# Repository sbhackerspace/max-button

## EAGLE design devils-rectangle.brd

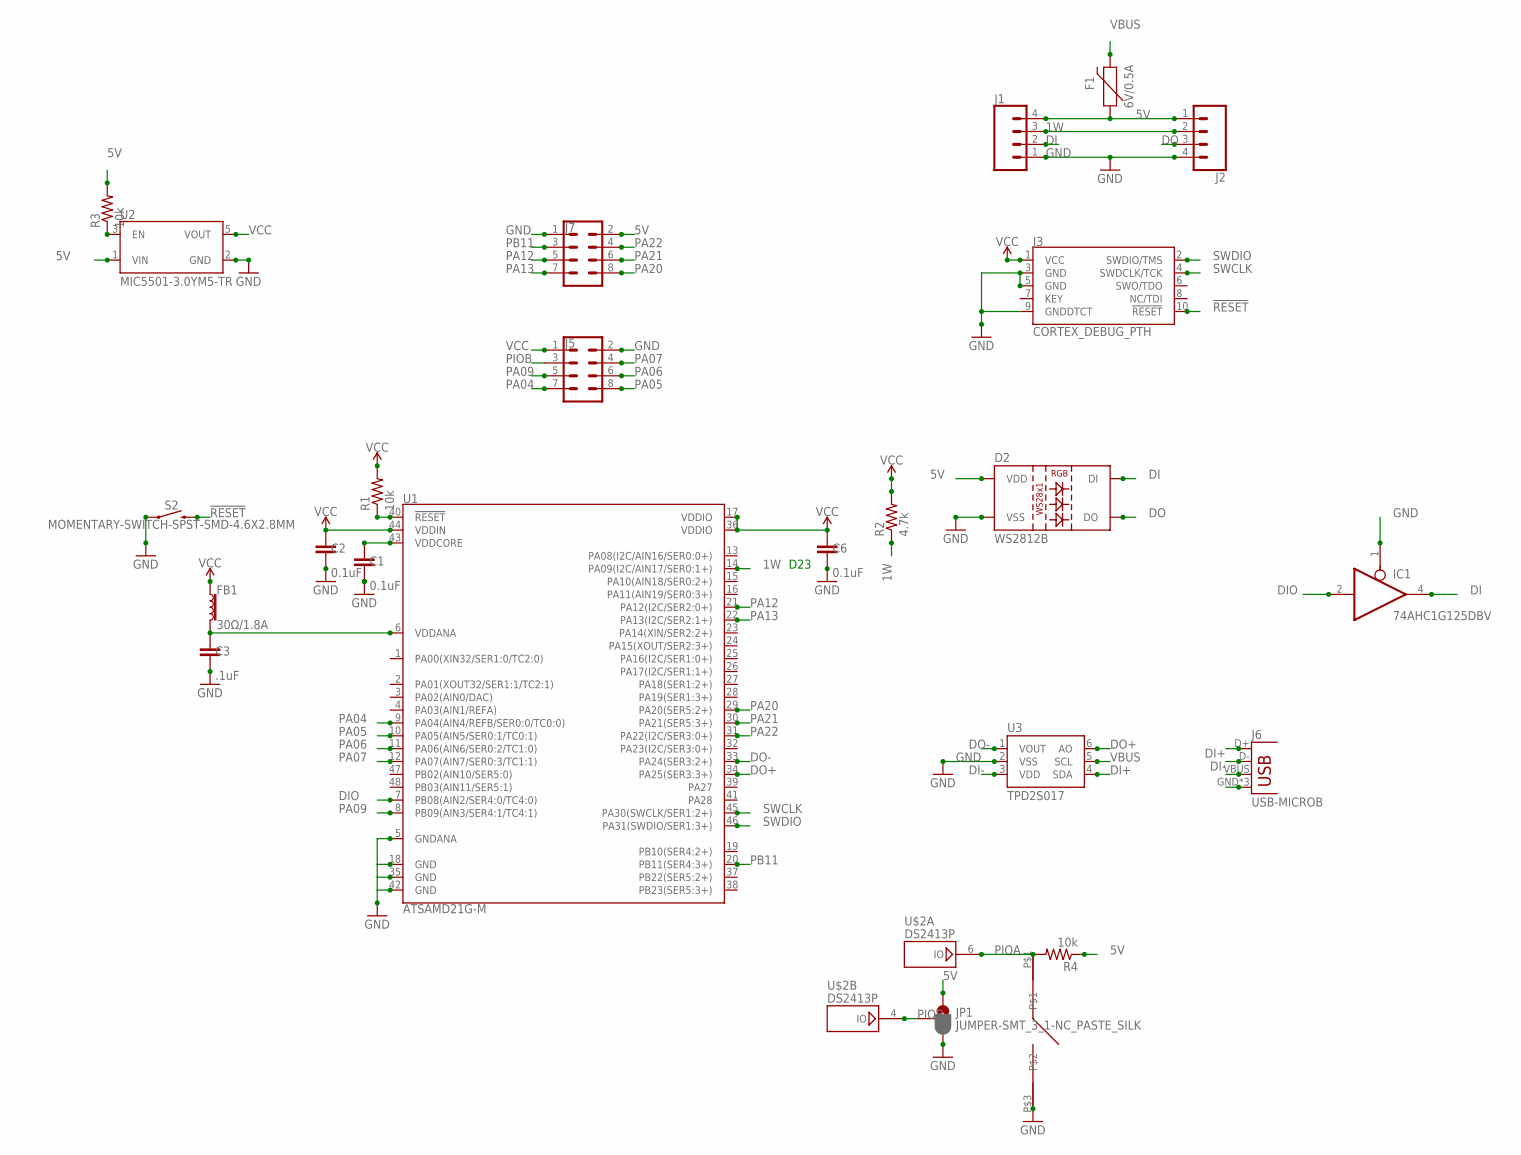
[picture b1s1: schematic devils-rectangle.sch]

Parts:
C1, C2, C6: 0.1uF; 0402
C3: .1uF; 0402
D2: WS2812B
F1: 6V/0.5A; 1206
FB1: 30Ω/1.8A; 0603
IC1: 74AHC1G125DBV; SOT23-5
J1, J2: CONN_04SMD2; 1X04_1MM_RA
J3: CORTEX_DEBUG_PTH; 2X5-PTH-1.27MM
J5, J7: CONN_04X2; 2X4
J6: USB-MICROB
JP1: JUMPER-SMT_3_1-NC_PASTE_SILK; SMT-JUMPER_3_1-NC_PASTE_SILK
R1, R3, R4: 10k; R0402
R2: 4.7k; R0402
S2: MOMENTARY-SWITCH-SPST-SMD-4.6X2.8MM; TACTILE_SWITCH_SMD_4.6X2.8MM
U1: ATSAMD21G-M; QFN-48
U2: MIC5501-3.0YM5-TR; SOT95P280X145-5N
U3: TPD2S017; SOT23-6
U$1: NOVELKEY
U$2: DS2413P; TSOC6

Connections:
1W: J1.3, J2.2, R2.1, U1.14 (PA09(I2C/AIN17/SER0:1+)), U$2.2 (1W)
5V: D2.1 (VDD), F1.1, IC1.5 (5V), J1.4, J2.1, J7.2, JP1.1, R3.2, R4.1, U2.1 (VIN)
!RESET: J3.10 (!RESET), R1.1, S2.3 (2), S2.4 (2), U1.40 (!RESET!)
DI: D2.4 (DI), IC1.4 (O), J1.2
DI+: J6.D+, U3.4 (SDA)
DI-: J6.D-, U3.3 (VDD)
DIO: IC1.2 (I), U1.7 (PB08(AIN2/SER4:0/TC4:0))
DO: D2.2 (DO), J2.3
DO+: U1.34 (PA25(SER3:3+)), U3.6 (AO)
DO-: U1.33 (PA24(SER3:2+)), U3.1 (VOUT)
GND: C1.2, C2.2, C3.2, C6.2, D2.3 (VSS), IC1.1 (OE), IC1.3 (GND), J1.1, J2.4, J3.3 (GND), J3.5 (GND), J3.9 (GNDDTCT), J5.2, J6.GND, J6.MT1 (GND), J6.MT2 (GND), J7.1, JP1.3, S2.1, S2.2 (1), U1.5 (GNDANA), U1.18 (GND), U1.35 (GND), U1.42 (GND), U2.2 (GND), U3.2 (VSS), U$1.P$3, U$2.1 (GND), U$2.5 (GND)
unnamed: R3.1, U2.3 (EN)
unnamed: C3.1, FB1.2, U1.6 (VDDANA)
unnamed: C1.1, U1.43 (VDDCORE)
PA04: J5.7, U1.9 (PA04(AIN4/REFB/SER0:0/TC0:0))
PA05: J5.8, U1.10 (PA05(AIN5/SER0:1/TC0:1))
PA06: J5.6, U1.11 (PA06(AIN6/SER0:2/TC1:0))
PA07: J5.4, U1.12 (PA07(AIN7/SER0:3/TC1:1))
PA09: J5.5, U1.8 (PB09(AIN3/SER4:1/TC4:1))
PA12: J7.5, U1.21 (PA12(I2C/SER2:0+))
PA13: J7.7, U1.22 (PA13(I2C/SER2:1+))
PA20: J7.8, U1.29 (PA20(SER5:2+))
PA21: J7.6, U1.30 (PA21(SER5:3+))
PA22: J7.4, U1.31 (PA22(I2C/SER3:0+))
PB11: J7.3, U1.20 (PB11(SER4:3+))
PIOA: R4.2, U$1.P$1, U$2.6 (IO)
PIOB: J5.3, JP1.2, U$2.4 (IO)
SWCLK: J3.4 (SWDCLK/TCK), U1.45 (PA30(SWCLK/SER1:2+))
SWDIO: J3.2 (SWDIO/TMS), U1.46 (PA31(SWDIO/SER1:3+))
VBUS: F1.2, J6.VBUS, U3.5 (SCL)
VCC: C2.1, C6.1, FB1.1, J3.1 (VCC), J5.1, R1.2, R2.2, U1.17 (VDDIO), U1.36 (VDDIO), U1.44 (VDDIN), U2.5 (VOUT)

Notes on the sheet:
D23

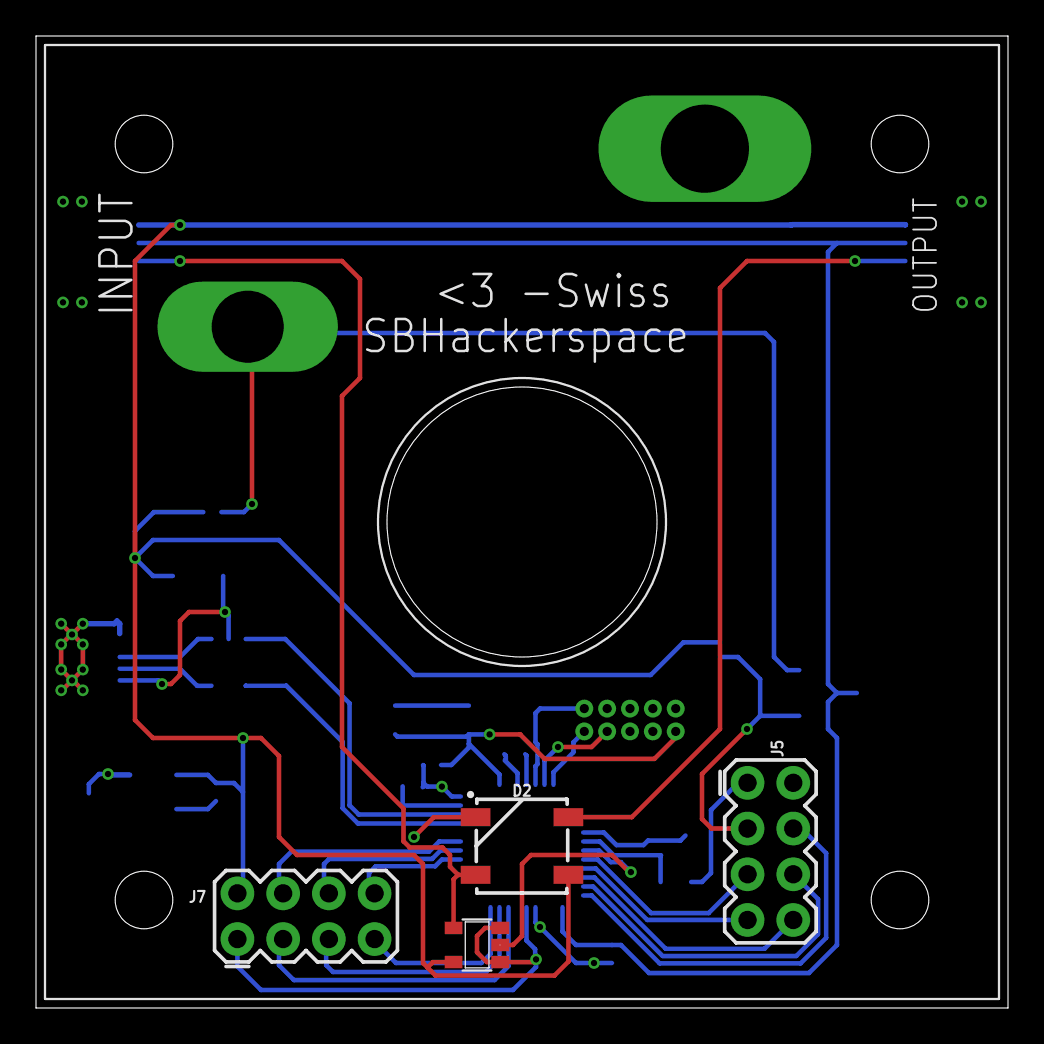
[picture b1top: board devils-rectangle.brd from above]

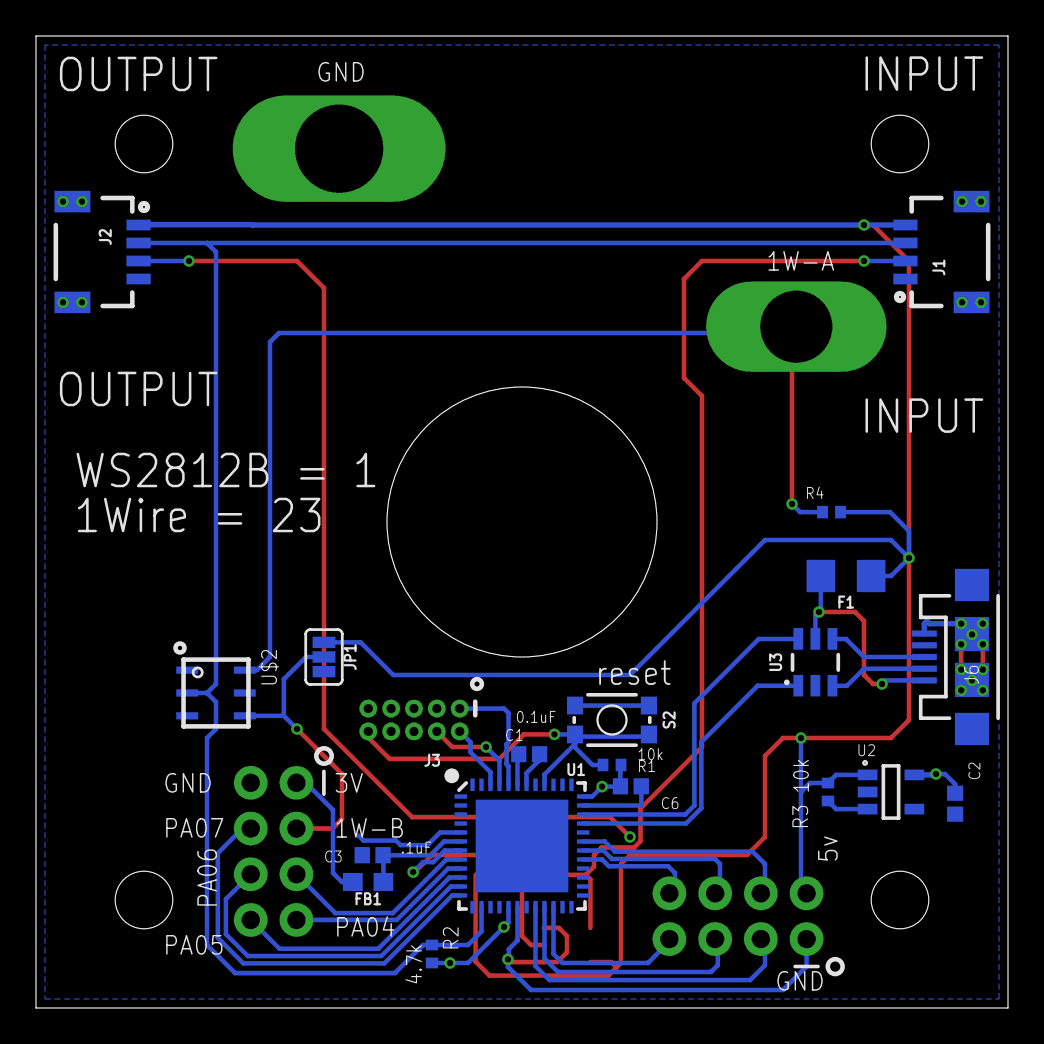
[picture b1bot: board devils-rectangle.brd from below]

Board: 2 copper layers, 54.0 x 54.0 mm, 25 parts (20 on the bottom side), 31 nets.

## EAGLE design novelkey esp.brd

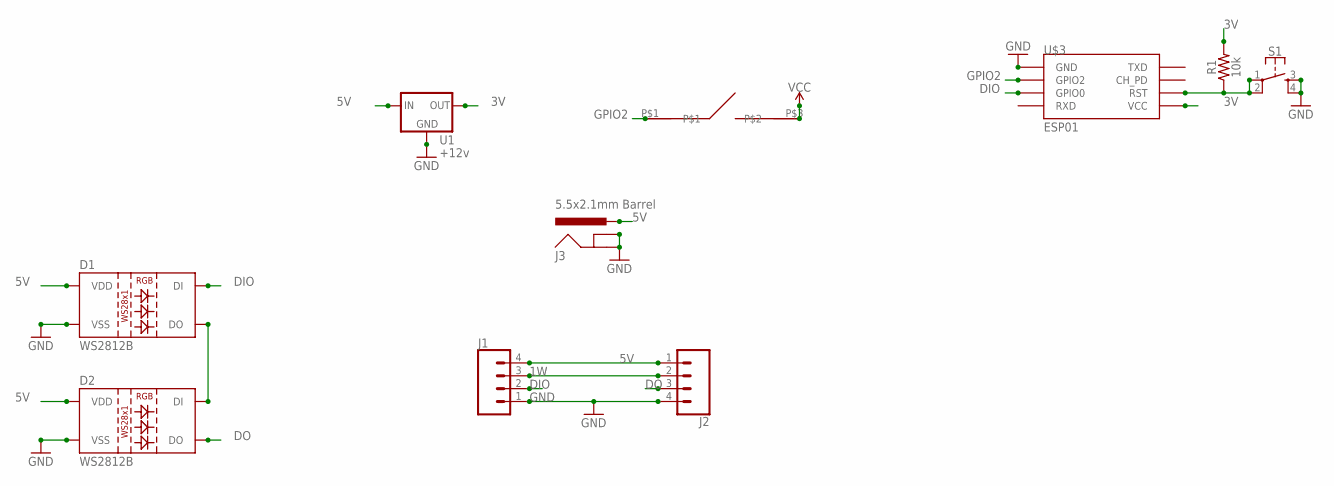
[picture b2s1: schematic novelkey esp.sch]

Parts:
D1, D2: WS2812B
J1, J2: CONN_04SMD2; 1X04_1MM_RA
J3: 5.5x2.1mm Barrel; POWER_JACK_SMD
R1: 10k; 0603
S1: MOMENTARY-SWITCH-SPST-2-SMD-4.6X2.8MM; TACTILE_SWITCH_SMD_4.6X2.8MM
U1: +12v; TO-252
U$1: NOVELKEY
U$3: ESP01

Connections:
1W: J1.3, J2.2
3V: R1.2, U1.2 (OUT), U$3.VCC
5V: D1.1 (VDD), D2.1 (VDD), J1.4, J2.1, J3.VIN0 (PWR), U1.1 (IN)
DIO: D1.4 (DI), J1.2, U$3.GPIO0
DO: D2.2 (DO), J2.3
GND: D1.3 (VSS), D2.3 (VSS), J1.1, J2.4, J3.GND (GNDBREAK), J3.P$4 (GND), S1.3, S1.4, U1.3 (GND), U$3.GND
GPIO2: U$1.P$1, U$3.GPIO2
unnamed: R1.1, S1.1, S1.2, U$3.RST
unnamed: D1.2 (DO), D2.4 (DI)
VCC: U$1.P$3

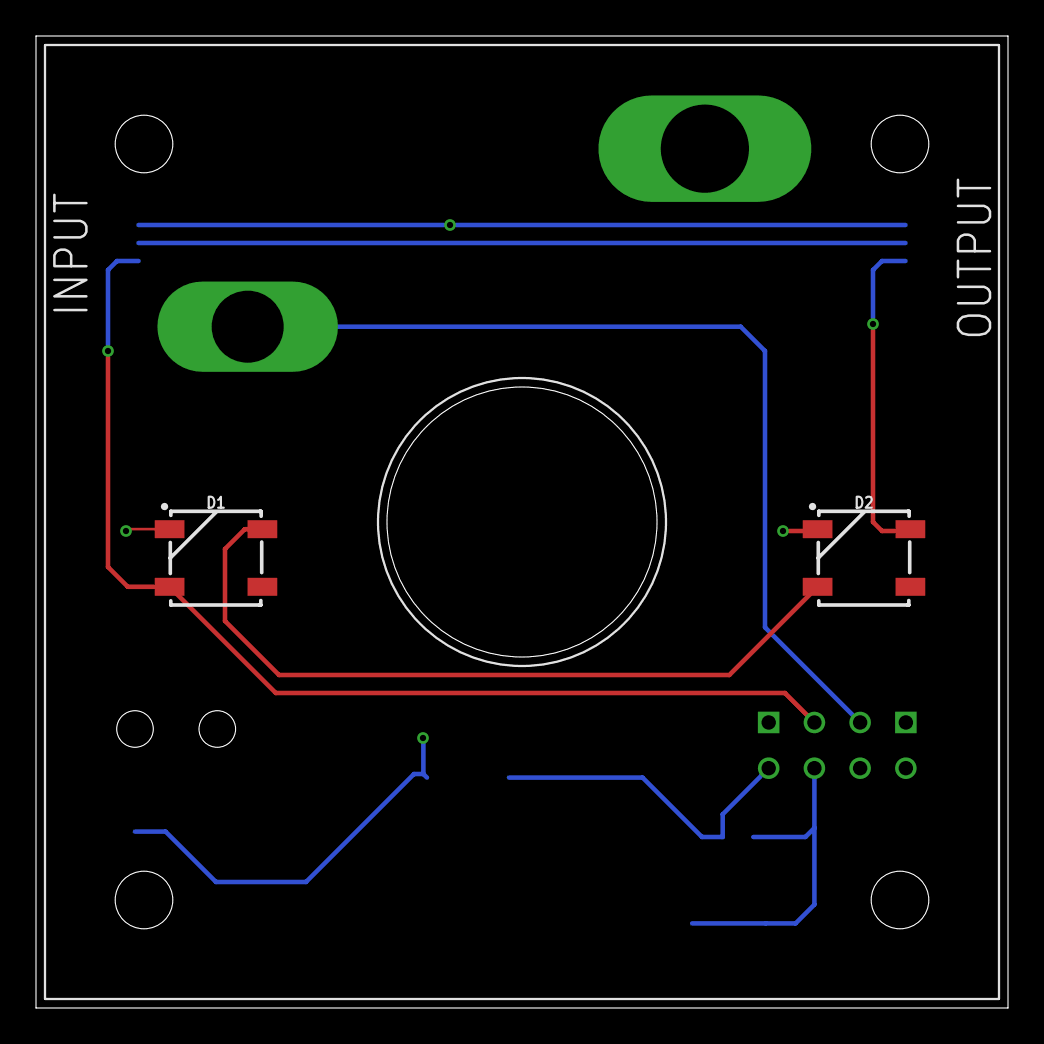
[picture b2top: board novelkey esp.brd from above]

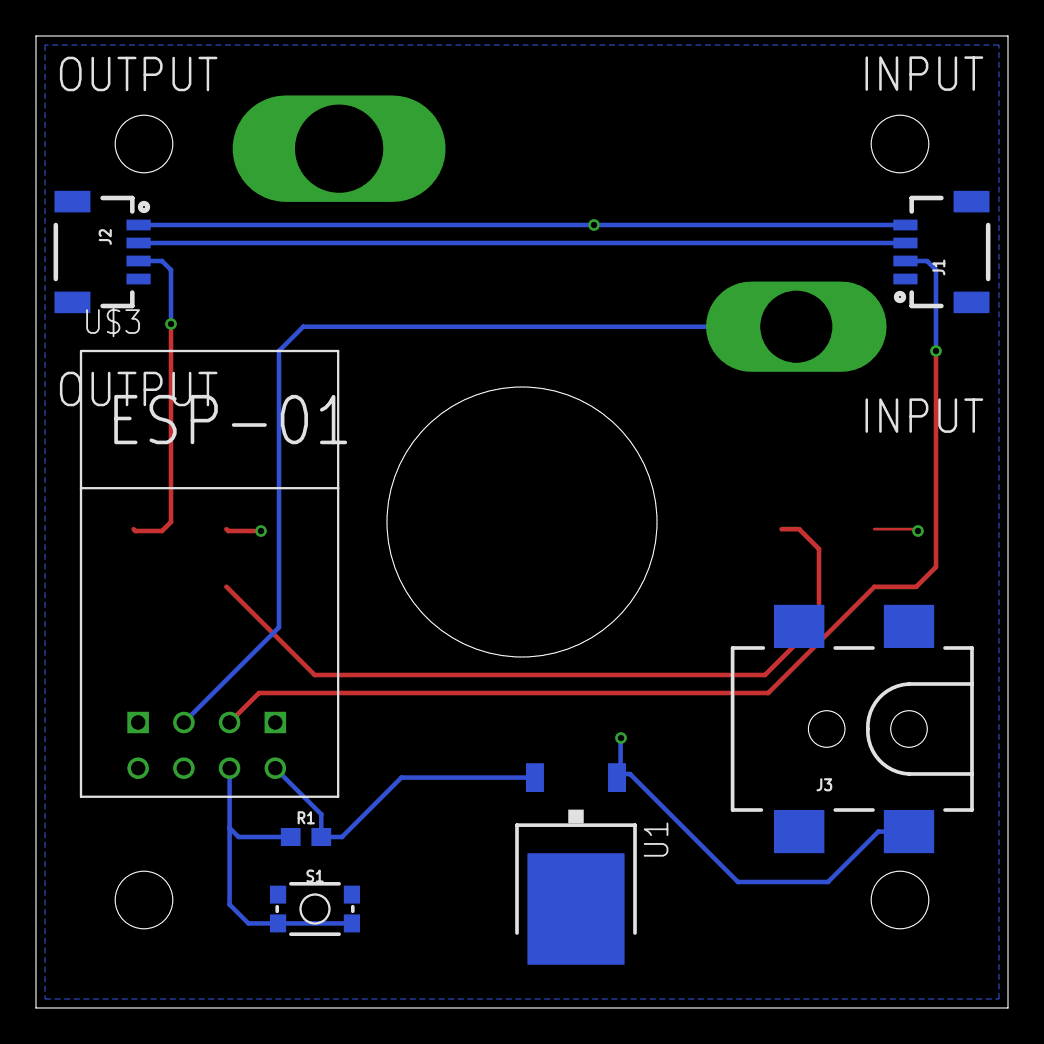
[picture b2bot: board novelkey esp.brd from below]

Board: 2 copper layers, 54.0 x 54.0 mm, 10 parts (7 on the bottom side), 9 nets.

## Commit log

2018-12-02 initial commit
    first revision of a breakout for the novelkey giant mx switches. The goal i sto create an inexpensive open source bussable breakout and controller board.
2018-12-02 removed ldo from top layer
    moved ldo to bottom layer. Removed unused nets from samd21g
2018-12-04 corrected button orientation
    placed novelkey on the correct side. reduced gpio by 2 pins to allow for tolerances. added mounting hole. updated routing.
2018-12-04 updated silkscreen
    updated silkscreen
2018-12-04 jplc gerbers
    generated a set of gerbers for JPLC PCBs
2018-12-06 added esp version and removed led
    added an esp8266 version of the board. Removed an LED from the samd21g version to move the LED to the empty space on the bottom of the novelkey.
2018-12-06 added vias below usb
    added gnd vias below the USB connector to improve mechanical stability.
2018-12-06 removed air wire
    removed air wire error on U$2
2018-12-06 added vias below bus connectors
    added vias below bus connectors to improve mechanical stability. Added ground symbol on bus connection net.
2018-12-06 fixed wire stub drc error
    removed wire stub on the USB connection vias.
2018-12-06 changed button from 3v to 5v
    moved button from 3v to 5v as the ds2413 is 5v tolerant and 5v is passed via the bus connector while 3v is not. Also negates the need for a vreg on each board.
2018-12-16 Rev 1 error fixes
    Updated ldo pull up resistor to Vin. Moved part values to layer that will show up in silkscreen. Updated capacitor footprint to match proper 0402 sizing. Replaced usb tvs/res IC. increased pullback.
2018-12-16 added BOM
    digikey cart bom
2018-12-16 rev 2 fab
    rev 2 sent to fab
2018-12-17 Updated Routing
    Updated routing to remove vias. Changed switch wiring to reflect ds2413 example circuit.
2018-12-17 added crystal
    added a 32khz crystal per the arduino zero spec. updated routing to fit the crystal and caps.
2018-12-17 moved digital traces
    moved digital IO traces to allow more space in between.
2018-12-17 updated ldo silkscreen
    updated silkscreen on the ldo to prevent overlaps
2018-12-17 added via to button pullup
    added a via to the button pullup to shorten distance to ground.
2018-12-17 minor cleanup
    minor cleanup
2018-12-17 schematic cleanup
    cleaned up schematic organization
2018-12-23 Reselved VDDCORE error - rev 3
    removed connection from vddcore to vcc that was causing a short burning out the internal arm regulator.
2019-01-06 backing up changes
    backing up changes
2019-01-06 updated gitignore and renamed project `
2019-01-06 updated naming
2019-08-24 updated bus switch
    updated bus switch to i2c to resolve arduino zero issue with onewire
2019-08-25 replaced i2c port expander
    replaced i2c port expander with an attiny85. added 3v pin to daughter board header.
2019-12-30 resolved routing errors
    resolved routing errors, added crystal, and tested. submitted to oshpark.
2020-01-17 Revert "sent to fab"
    This reverts commit 4395226a2b02ff09c6c76ca9ff8e8c36c153bf92, reversing
    changes made to 6eea5bdc47f5d2efe417c0b61bc92f1f556a86fc.
2020-01-17 sent to fab
    sent to fab, errors on board
2020-01-17 rev 3
    fixed errors, sent to fab.
2020-01-17 silkscreen update
    scilkscreen now has I/O definitions
2020-01-18 fixed errors
    fixed errors, added breakout for PIOB on DS2413, updated silk screen

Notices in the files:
parts and their libraries:
SparkFun-Connectors: Licensing: Creative Commons ShareAlike 4.0 International - https://creativecommons.org/licenses/by-sa/4.0
